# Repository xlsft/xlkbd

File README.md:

# XLKBD O1-B

65-key ortholinear wireless mechanical keyboard with 11x55 color matrix and 2500mah battery
designed and assembled by xlsft in russia with <3

# Renders

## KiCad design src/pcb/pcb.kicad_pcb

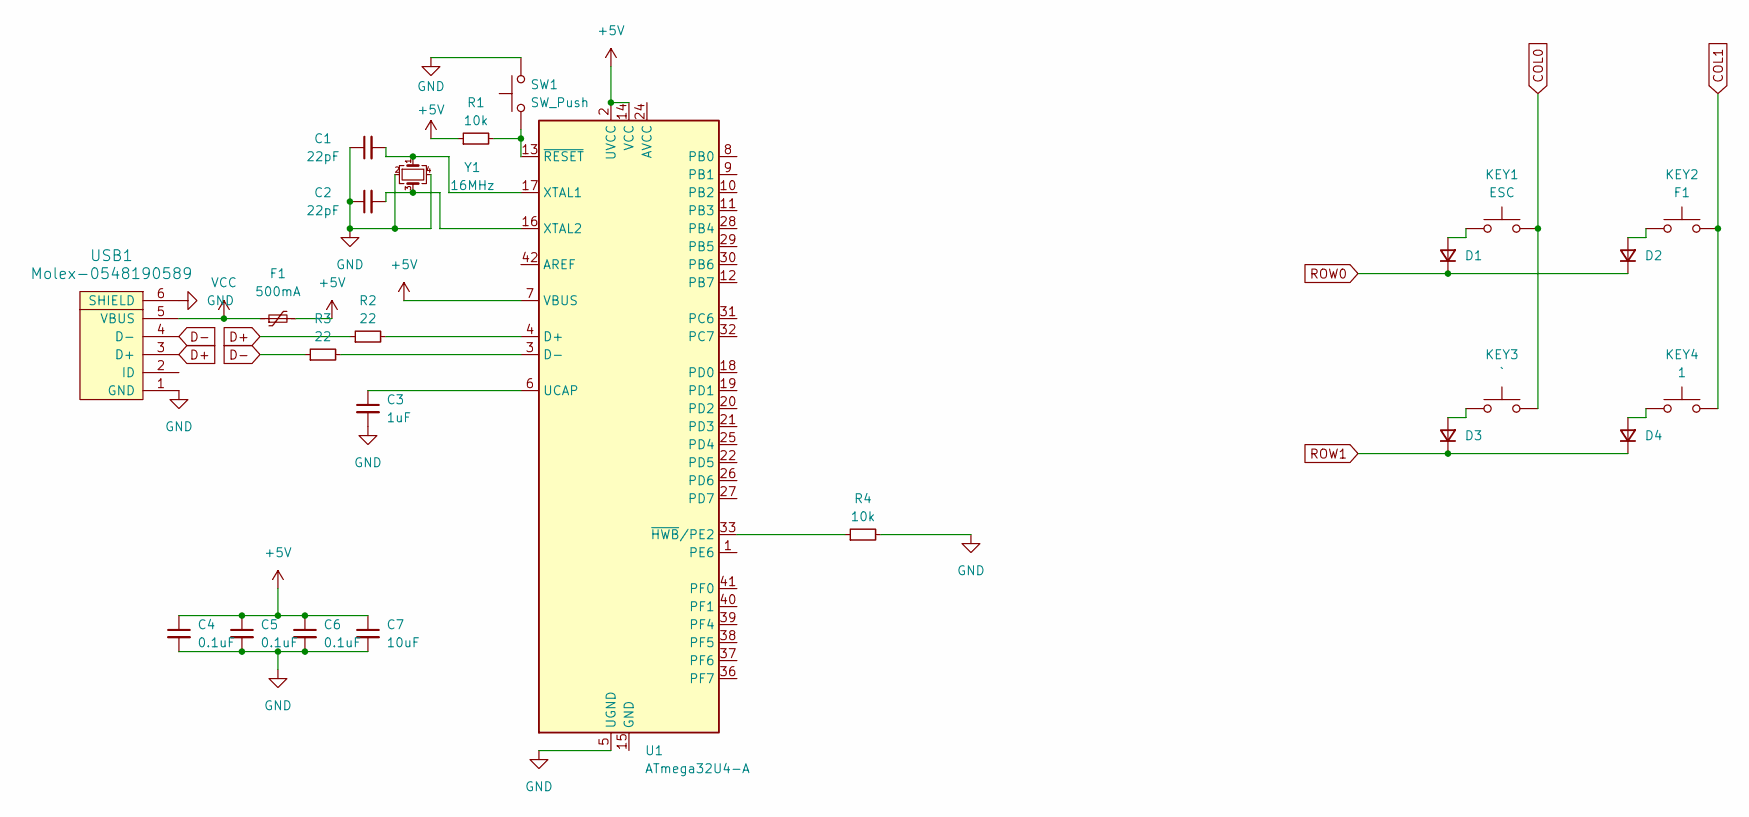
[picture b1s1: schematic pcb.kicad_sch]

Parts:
C1, C2: 22pF; C_0805_2012Metric
C3: 1uF; C_0805_2012Metric
C4, C5, C6: 0.1uF; C_0805_2012Metric
C7: 10uF; C_0805_2012Metric
D1, D2, D3, D4: D_0805_2012Metric
F1: 500mA; Fuse_1206_3216Metric
KEY1: ESC; MX-Hotswap-1U
KEY2: F1; MX-Hotswap-1U
KEY3: `; MX-Hotswap-1U
KEY4: 1; MX-Hotswap-1U
R1, R4: 10k; R_0805_2012Metric
R2, R3: 22; R_0805_2012Metric
SW1: SW_Push; SKQG-1155865
U1: ATmega32U4-A; TQFP-44_10x10mm_P0.8mm
USB1: Molex-0548190589
Y1: 16MHz; Crystal_SMD_3225-4Pin_3.2x2.5mm

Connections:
+5V: C4.1, C5.1, C6.1, C7.1, F1.2, R1.1, U1.2 (UVCC), U1.7 (VBUS), U1.14 (VCC), U1.34 (VCC)
COL0: KEY1.2, KEY3.2
COL1: KEY2.2, KEY4.2
D+: R2.1, USB1.3 (D+)
D-: R3.1, USB1.4 (D-)
GND: C1.1, C2.1, C3.2, C4.2, C5.2, C6.2, C7.2, R4.2, SW1.2, U1.5 (UGND), USB1.1 (GND), USB1.6 (SHIELD), Y1.2, Y1.4
unnamed: D1.2 (A), KEY1.1
unnamed: D2.2 (A), KEY2.1
unnamed: D3.2 (A), KEY3.1
unnamed: D4.2 (A), KEY4.1
unnamed: U1.24 (AVCC), U1.44 (AVCC)
unnamed: R2.2, U1.4 (D+)
unnamed: R3.2, U1.3 (D-)
unnamed: U1.15 (GND), U1.23 (GND), U1.35 (GND), U1.43 (GND)
unnamed: C3.1, U1.6 (UCAP)
unnamed: C1.2, U1.17 (XTAL1), Y1.1
unnamed: C2.2, U1.16 (XTAL2), Y1.3
unnamed: R4.1, U1.33 (~HWB/PE2)
unnamed: R1.2, SW1.1, U1.13 (~RESET)
ROW0: D1.1 (K), D2.1 (K)
ROW1: D3.1 (K), D4.1 (K)
VCC: F1.1, USB1.5 (VBUS)

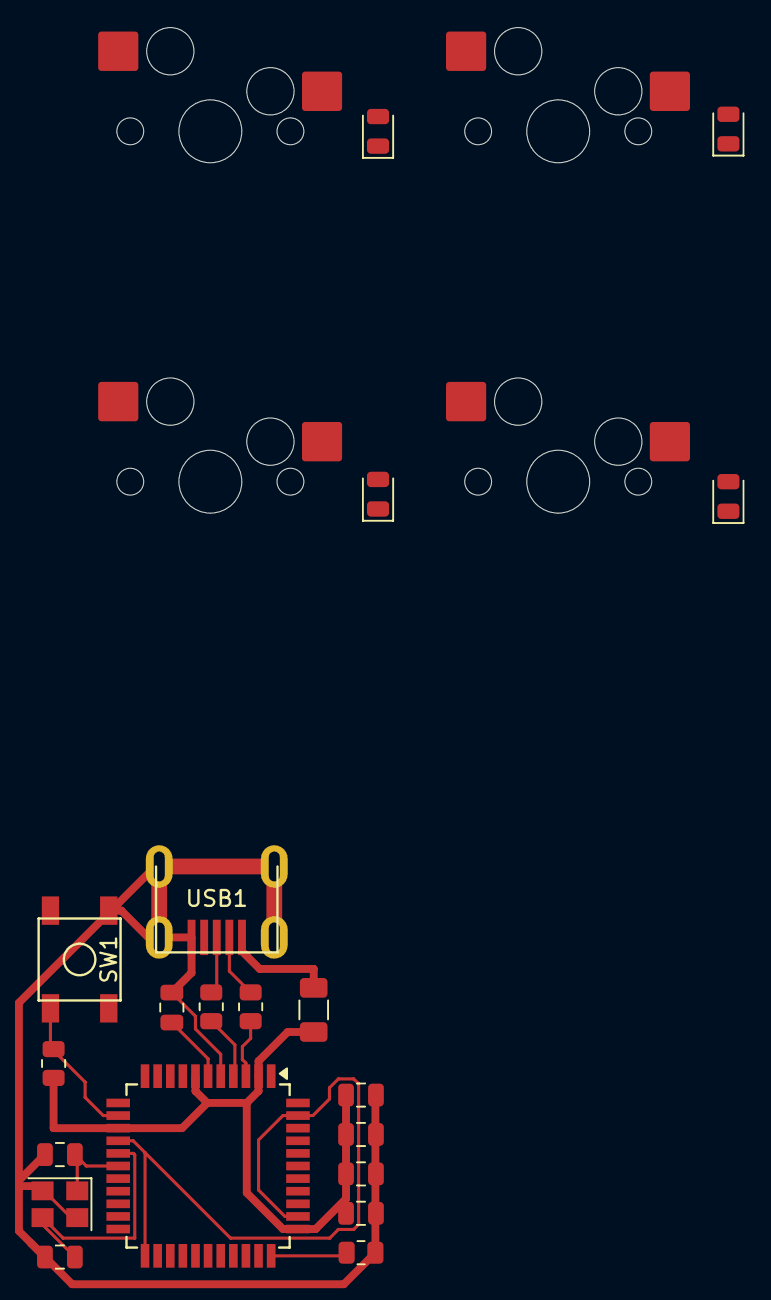
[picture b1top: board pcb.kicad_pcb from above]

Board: 2 copper layers, 24 parts (0 on the bottom side), 22 nets.

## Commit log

2024-12-16 init: pcb kicad layout
2024-12-16 feat: kicad plugins
2024-12-16 feat: MX_V2 footprint library replacment
2024-12-16 feat: v.-1 usb connection with controller
2025-01-27 init: xlkbd v1
2025-01-28 feat: :sparkles: KLE layout raw data, AI03 plate, [board]: connect usb-type-c to esp32 and x2 `TCA8418RTWR` to keayboard matrix
2025-03-03 feat: :zap: board rev. 0
2025-03-03 feat:
2025-03-06 feat: :zap: possibly working revision, but need to check
2025-06-10 feat: O1-B
2025-06-28 feat: cad model
